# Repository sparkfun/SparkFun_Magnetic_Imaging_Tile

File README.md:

SparkFun Magnetic Imaging Tile - 8x8
========================================

[*SparkFun Magnetic Imaging Tile - 8x8 (SEN-26092)*](https://www.sparkfun.com/products/26092)

The Magnetic Imaging Tile uses an array of 64 hall effect sensors to convert magnetic fields to the visual spectrum. That's right! You can now see magnetic fields in real time! As is to be expected, there are caveats: the magnetic sensors used on the tile are some of the most sensitive on the market but you need to be within 1 to 2 centimeters of the tile to get a good image.

This is a board intended to function as a "magnetic field camera" to visualize magnetic fields.

This is an endorsed fork and collaboration of [Peter Jansen's work](https://hackaday.io/project/18518-iteration-8/log/91551-a-third-high-speed-magnetic-imager-tile). All credit goes to him! SparkX has re-designed the PCB for DFM and simplified some of the platform interfacing code.

### Version 3.0

The major advancement of v3.0 is a dramatic increase in the speed with which the tile data can be read out. ~2000 frames per second (fps) can be achieved which allows visualizing even quickly varying fields (e.g. those in a 60Hz transformer, or a moving motor). Version 3.0 reduces the size of the tile to an 8x8 grid of hall effect sensors (64 total), arrayed in a 4mm grid.  The boards is tile-able with up to 4 of the boards tileable with minimal borders to create a 16x16 array.

For more information (and a video of the v3.0 tile in use), please see:
https://hackaday.io/project/18518-iteration-8/log/91551-a-third-high-speed-magnetic-imager-tile-draft

Repository Contents
-------------------
* **.github/workflows** - YAML files used for GitHub Actions and GitHub Pages/mkdocs
* **/Hardware** - Eagle design files (.brd, .sch)
* **/Production** - Production panel files (.brd)
* **/Software** - Related software for the Magnetic Imaging Tile
* **/docs** - Online documentation files
  * **/assets** - Folder containing all the file assets used for product documentation
    * **/board_files** - Copy of design files used for product documentation
    * **/component_documentation** - Datasheets and manuals for hardware components
    * **/img** - Images for product documentation
  * **/github** - Files stating how to contribute and filing issues used for product documentation
  * **/javascript** - Folder containing custom javascript used for product documentation
  * **/stylesheet** - Folder containing CSS files used for product documentation
* **/overrides** - Customization files used for product documentation
  * **/.icons** - Icons used for GitHub used for product documentation
  * **./partials** - Used for product documentation

License Information
-------------------

This product is _**open source**_!

Please review the LICENSE.md file for license information.

If you have any questions or concerns on licensing, please contact technical support in our [SparkFun forums](https://community.sparkfun.com/c/community/general-chit-chat/37.)

Please use, reuse, and modify these files as you see fit. Please maintain attribution to SparkFun Electronics and release any derivative under the same license.

Disclaimer
-------------------

**DISCLAIMER OF WARRANTIES AND LIMITATION OF LIABILITY.**

UNLESS OTHERWISE SEPARATELY UNDERTAKEN BY THE LICENSOR, TO THE EXTENT POSSIBLE, THE LICENSOR OFFERS THE LICENSED MATERIAL AS-IS AND AS-AVAILABLE, AND MAKES NO REPRESENTATIONS OR WARRANTIES OF ANY KIND CONCERNING THE LICENSED MATERIAL, WHETHER EXPRESS, IMPLIED, STATUTORY, OR OTHER. THIS INCLUDES, WITHOUT LIMITATION, WARRANTIES OF TITLE, MERCHANTABILITY, FITNESS FOR A PARTICULAR PURPOSE, NON-INFRINGEMENT, ABSENCE OF LATENT OR OTHER DEFECTS, ACCURACY, OR THE PRESENCE OR ABSENCE OF ERRORS, WHETHER OR NOT KNOWN OR DISCOVERABLE. WHERE DISCLAIMERS OF WARRANTIES ARE NOT ALLOWED IN FULL OR IN PART, THIS DISCLAIMER MAY NOT APPLY TO YOU.

TO THE EXTENT POSSIBLE, IN NO EVENT WILL THE LICENSOR BE LIABLE TO YOU ON ANY LEGAL THEORY (INCLUDING, WITHOUT LIMITATION, NEGLIGENCE) OR OTHERWISE FOR ANY DIRECT, SPECIAL, INDIRECT, INCIDENTAL, CONSEQUENTIAL, PUNITIVE, EXEMPLARY, OR OTHER LOSSES, COSTS, EXPENSES, OR DAMAGES ARISING OUT OF THIS PUBLIC LICENSE OR USE OF THE LICENSED MATERIAL, EVEN IF THE LICENSOR HAS BEEN ADVISED OF THE POSSIBILITY OF SUCH LOSSES, COSTS, EXPENSES, OR DAMAGES. WHERE A LIMITATION OF LIABILITY IS NOT ALLOWED IN FULL OR IN PART, THIS LIMITATION MAY NOT APPLY TO YOU.

THE DISCLAIMER OF WARRANTIES AND LIMITATION OF LIABILITY PROVIDED ABOVE SHALL BE INTERPRETED IN A MANNER THAT, TO THE EXTENT POSSIBLE, MOST CLOSELY APPROXIMATES AN ABSOLUTE DISCLAIMER AND WAIVER OF ALL LIABILITY.

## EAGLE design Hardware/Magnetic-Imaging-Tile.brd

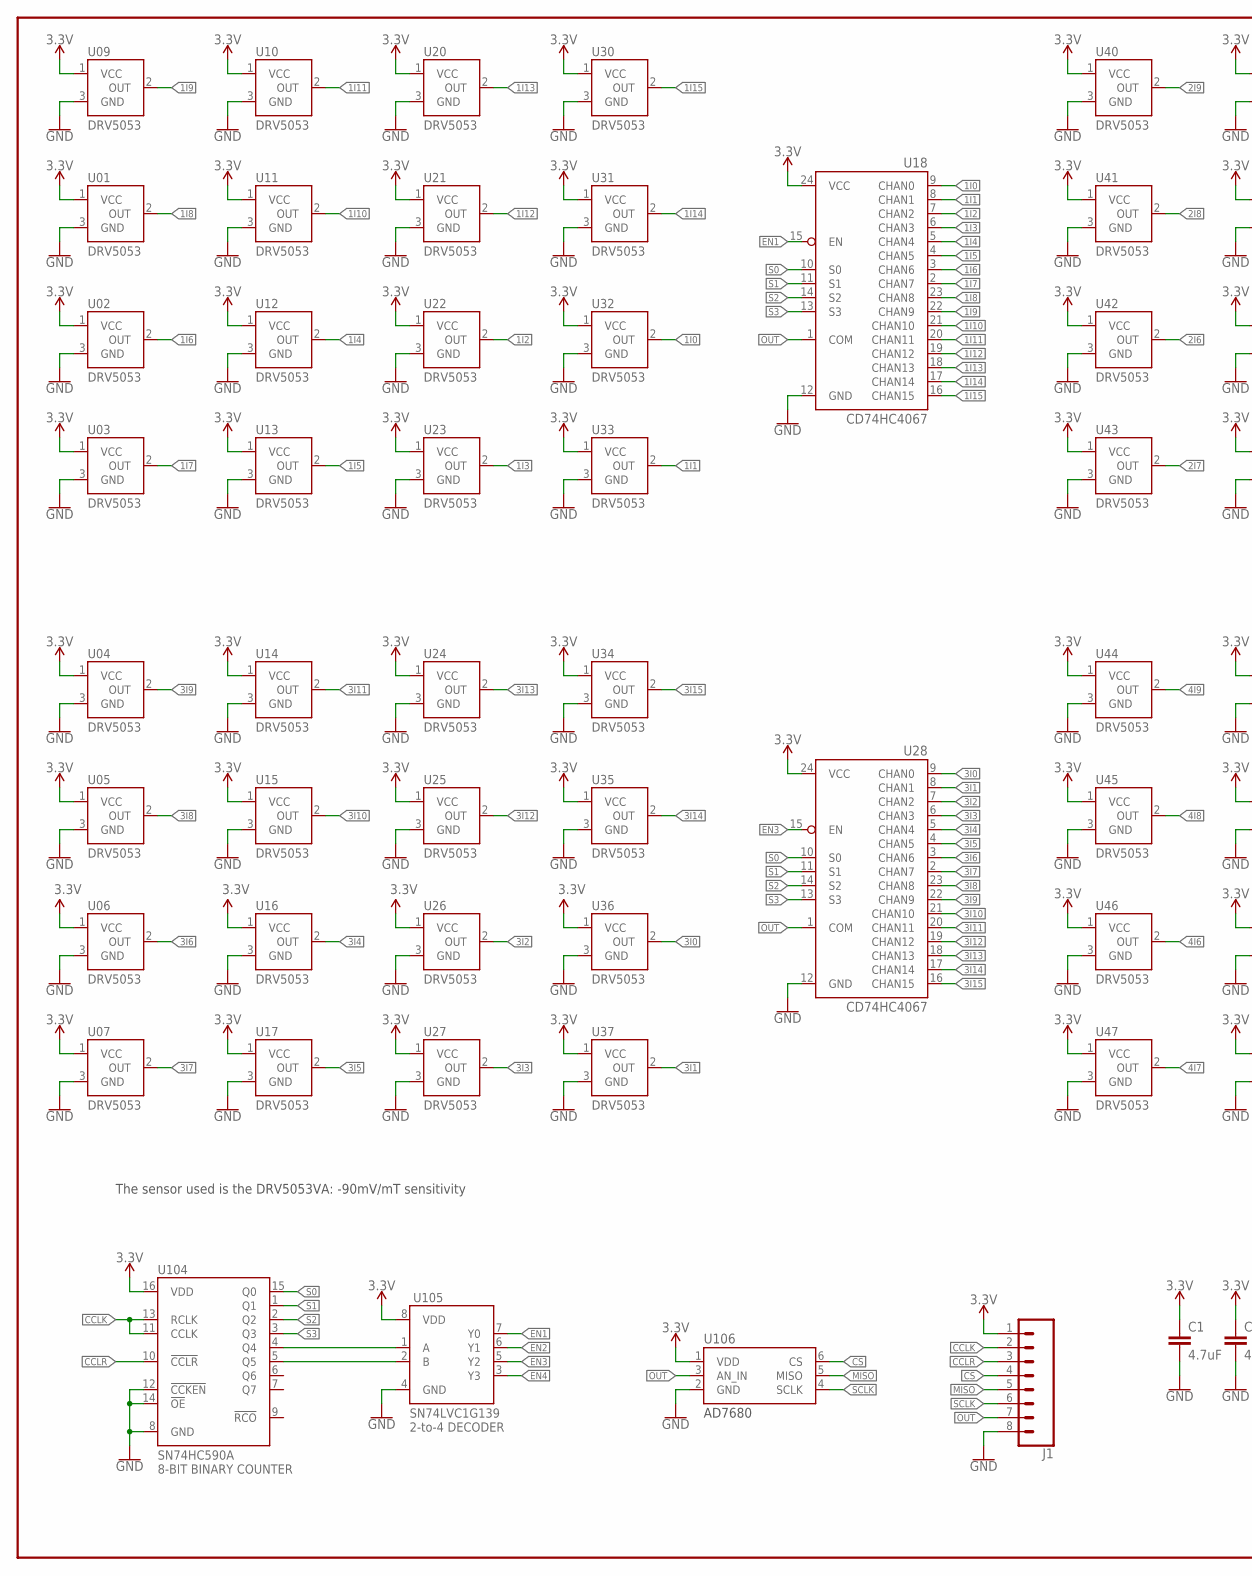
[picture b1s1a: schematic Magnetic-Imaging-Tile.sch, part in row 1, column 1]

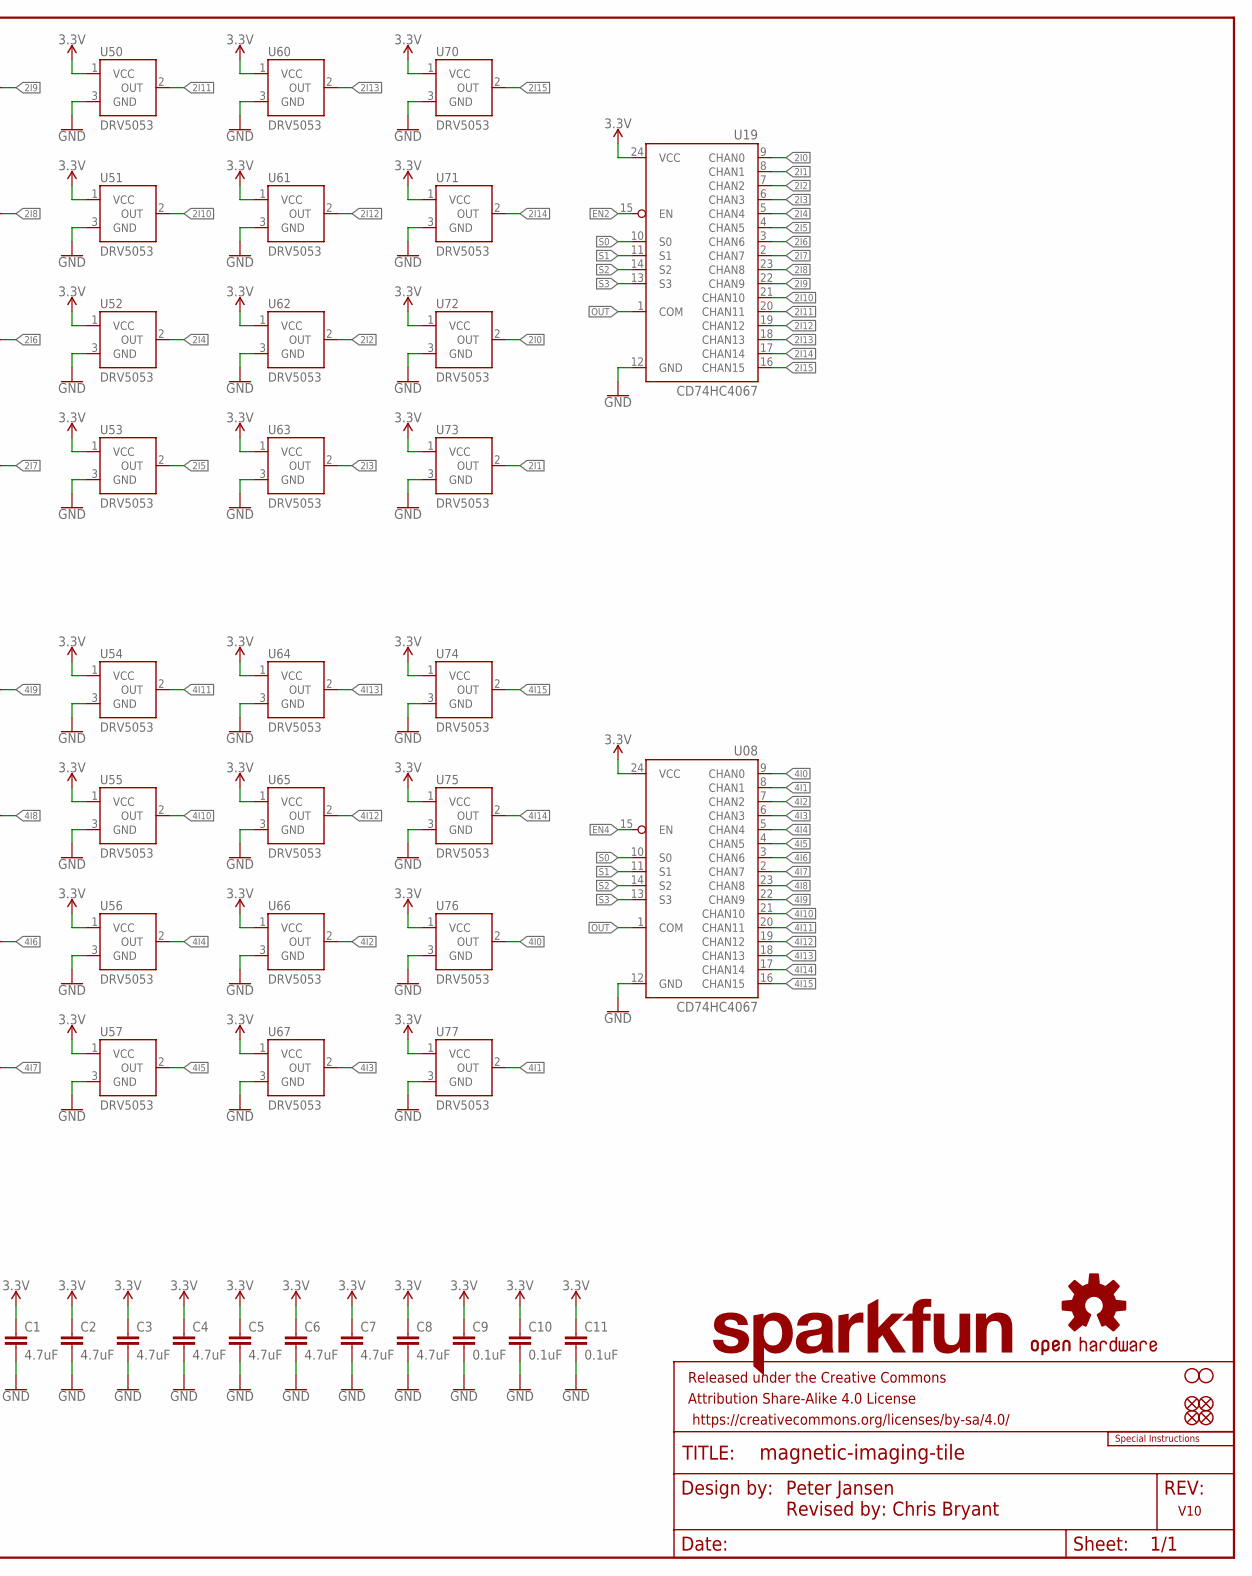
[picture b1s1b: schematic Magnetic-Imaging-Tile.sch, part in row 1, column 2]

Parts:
C1, C2, C3, C4, C5, C6, C7, C8: 4.7uF; 0603
C9, C10, C11: 0.1uF; 0603
FD1, FD2, FD3, FD4: FIDUCIALUFIDUCIAL; FIDUCIAL-MICRO
FRAME1: FRAME-LEDGER; CREATIVE_COMMONS
H1, H2: STAND-OFF
J1: CONN_08LOCK_NO_SILK; 1X08_LOCK_NO_SILK
LOGO1: SPECIAL_INSTRUCTIONS-ORDERING; ORDERING_INSTRUCTIONS
LOGO3: SFE_LOGO_NAME.1_INCH; SFE_LOGO_NAME_.1
LOGO4: OSHW-LOGOS; OSHW-LOGO-S
U01, U02, U03, U04, U05, U06, U07, U09, U10, U11, U12, U13, U14, U15, U16, U17, U20, U21, U22, U23, U24, U25, U26, U27, U30, U31, U32, U33, U34, U35, U36, U37, U40, U41, U42, U43, U44, U45, U46, U47, U50, U51, U52, U53, U54, U55, U56, U57, U60, U61, U62, U63, U64, U65, U66, U67, U70, U71, U72, U73, U74, U75, U76, U77: DRV5053; SOT23-3
U08, U18, U19, U28: CD74HC4067; SSOP24
U104: SN74HC590A; SO16
U105: SN74LVC1G139; SM8
U106: AD7680; SOT23-6

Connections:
1I0: U18.9 (CHAN0), U32.2 (OUT)
1I1: U18.8 (CHAN1), U33.2 (OUT)
1I2: U18.7 (CHAN2), U22.2 (OUT)
1I3: U18.6 (CHAN3), U23.2 (OUT)
1I4: U12.2 (OUT), U18.5 (CHAN4)
1I5: U13.2 (OUT), U18.4 (CHAN5)
1I6: U02.2 (OUT), U18.3 (CHAN6)
1I7: U03.2 (OUT), U18.2 (CHAN7)
1I8: U01.2 (OUT), U18.23 (CHAN8)
1I9: U09.2 (OUT), U18.22 (CHAN9)
1I10: U11.2 (OUT), U18.21 (CHAN10)
1I11: U10.2 (OUT), U18.20 (CHAN11)
1I12: U18.19 (CHAN12), U21.2 (OUT)
1I13: U18.18 (CHAN13), U20.2 (OUT)
1I14: U18.17 (CHAN14), U31.2 (OUT)
1I15: U18.16 (CHAN15), U30.2 (OUT)
2I0: U19.9 (CHAN0), U72.2 (OUT)
2I1: U19.8 (CHAN1), U73.2 (OUT)
2I2: U19.7 (CHAN2), U62.2 (OUT)
2I3: U19.6 (CHAN3), U63.2 (OUT)
2I4: U19.5 (CHAN4), U52.2 (OUT)
2I5: U19.4 (CHAN5), U53.2 (OUT)
2I6: U19.3 (CHAN6), U42.2 (OUT)
2I7: U19.2 (CHAN7), U43.2 (OUT)
2I8: U19.23 (CHAN8), U41.2 (OUT)
2I9: U19.22 (CHAN9), U40.2 (OUT)
2I10: U19.21 (CHAN10), U51.2 (OUT)
2I11: U19.20 (CHAN11), U50.2 (OUT)
2I12: U19.19 (CHAN12), U61.2 (OUT)
2I13: U19.18 (CHAN13), U60.2 (OUT)
2I14: U19.17 (CHAN14), U71.2 (OUT)
2I15: U19.16 (CHAN15), U70.2 (OUT)
3.3V: C1.1, C2.1, C3.1, C4.1, C5.1, C6.1, C7.1, C8.1, C9.1, C10.1, C11.1, J1.1, U01.1 (VCC), U02.1 (VCC), U03.1 (VCC), U04.1 (VCC), U05.1 (VCC), U06.1 (VCC), U07.1 (VCC), U08.24 (VCC), U09.1 (VCC), U10.1 (VCC), U11.1 (VCC), U12.1 (VCC), U13.1 (VCC), U14.1 (VCC), U15.1 (VCC), U16.1 (VCC), U17.1 (VCC), U18.24 (VCC), U19.24 (VCC), U20.1 (VCC), U21.1 (VCC), U22.1 (VCC), U23.1 (VCC), U24.1 (VCC), U25.1 (VCC), U26.1 (VCC), U27.1 (VCC), U28.24 (VCC), U30.1 (VCC), U31.1 (VCC), U32.1 (VCC), U33.1 (VCC), U34.1 (VCC), U35.1 (VCC), U36.1 (VCC), U37.1 (VCC), U40.1 (VCC), U41.1 (VCC), U42.1 (VCC), U43.1 (VCC), U44.1 (VCC), U45.1 (VCC), U46.1 (VCC), U47.1 (VCC), U50.1 (VCC), U51.1 (VCC), U52.1 (VCC), U53.1 (VCC), U54.1 (VCC), U55.1 (VCC), U56.1 (VCC), U57.1 (VCC), U60.1 (VCC), U61.1 (VCC), U62.1 (VCC), U63.1 (VCC), U64.1 (VCC), U65.1 (VCC), U66.1 (VCC), U67.1 (VCC), U70.1 (VCC), U71.1 (VCC), U72.1 (VCC), U73.1 (VCC), U74.1 (VCC), U75.1 (VCC), U76.1 (VCC), U77.1 (VCC), U104.16 (VDD), U105.8 (VDD), U106.1 (VDD)
3I0: U28.9 (CHAN0), U36.2 (OUT)
3I1: U28.8 (CHAN1), U37.2 (OUT)
3I2: U26.2 (OUT), U28.7 (CHAN2)
3I3: U27.2 (OUT), U28.6 (CHAN3)
3I4: U16.2 (OUT), U28.5 (CHAN4)
3I5: U17.2 (OUT), U28.4 (CHAN5)
3I6: U06.2 (OUT), U28.3 (CHAN6)
3I7: U07.2 (OUT), U28.2 (CHAN7)
3I8: U05.2 (OUT), U28.23 (CHAN8)
3I9: U04.2 (OUT), U28.22 (CHAN9)
3I10: U15.2 (OUT), U28.21 (CHAN10)
3I11: U14.2 (OUT), U28.20 (CHAN11)
3I12: U25.2 (OUT), U28.19 (CHAN12)
3I13: U24.2 (OUT), U28.18 (CHAN13)
3I14: U28.17 (CHAN14), U35.2 (OUT)
3I15: U28.16 (CHAN15), U34.2 (OUT)
4I0: U08.9 (CHAN0), U76.2 (OUT)
4I1: U08.8 (CHAN1), U77.2 (OUT)
4I2: U08.7 (CHAN2), U66.2 (OUT)
4I3: U08.6 (CHAN3), U67.2 (OUT)
4I4: U08.5 (CHAN4), U56.2 (OUT)
4I5: U08.4 (CHAN5), U57.2 (OUT)
4I6: U08.3 (CHAN6), U46.2 (OUT)
4I7: U08.2 (CHAN7), U47.2 (OUT)
4I8: U08.23 (CHAN8), U45.2 (OUT)
4I9: U08.22 (CHAN9), U44.2 (OUT)
4I10: U08.21 (CHAN10), U55.2 (OUT)
4I11: U08.20 (CHAN11), U54.2 (OUT)
4I12: U08.19 (CHAN12), U65.2 (OUT)
4I13: U08.18 (CHAN13), U64.2 (OUT)
4I14: U08.17 (CHAN14), U75.2 (OUT)
4I15: U08.16 (CHAN15), U74.2 (OUT)
!CCLR: J1.3, U104.10 (!CCLR)
!EN1: U18.15 (EN), U105.7 (Y0)
!EN2: U19.15 (EN), U105.6 (Y1)
!EN3: U28.15 (EN), U105.5 (Y2)
!EN4: U08.15 (EN), U105.3 (Y3)
CCLK: J1.2, U104.11 (CCLK), U104.13 (RCLK)
CS: J1.4, U106.6 (CS)
GND: C1.2, C2.2, C3.2, C4.2, C5.2, C6.2, C7.2, C8.2, C9.2, C10.2, C11.2, J1.8, U01.3 (GND), U02.3 (GND), U03.3 (GND), U04.3 (GND), U05.3 (GND), U06.3 (GND), U07.3 (GND), U08.12 (GND), U09.3 (GND), U10.3 (GND), U11.3 (GND), U12.3 (GND), U13.3 (GND), U14.3 (GND), U15.3 (GND), U16.3 (GND), U17.3 (GND), U18.12 (GND), U19.12 (GND), U20.3 (GND), U21.3 (GND), U22.3 (GND), U23.3 (GND), U24.3 (GND), U25.3 (GND), U26.3 (GND), U27.3 (GND), U28.12 (GND), U30.3 (GND), U31.3 (GND), U32.3 (GND), U33.3 (GND), U34.3 (GND), U35.3 (GND), U36.3 (GND), U37.3 (GND), U40.3 (GND), U41.3 (GND), U42.3 (GND), U43.3 (GND), U44.3 (GND), U45.3 (GND), U46.3 (GND), U47.3 (GND), U50.3 (GND), U51.3 (GND), U52.3 (GND), U53.3 (GND), U54.3 (GND), U55.3 (GND), U56.3 (GND), U57.3 (GND), U60.3 (GND), U61.3 (GND), U62.3 (GND), U63.3 (GND), U64.3 (GND), U65.3 (GND), U66.3 (GND), U67.3 (GND), U70.3 (GND), U71.3 (GND), U72.3 (GND), U73.3 (GND), U74.3 (GND), U75.3 (GND), U76.3 (GND), U77.3 (GND), U104.8 (GND), U104.12 (!CCKEN), U104.14 (!OE), U105.4 (GND), U106.2 (GND)
MISO: J1.5, U106.5 (MISO)
unnamed: U104.4 (Q4), U105.1 (A)
unnamed: U104.5 (Q5), U105.2 (B)
OUT: J1.7, U08.1 (COM), U18.1 (COM), U19.1 (COM), U28.1 (COM), U106.3 (AN_IN)
S0: U08.10 (S0), U18.10 (S0), U19.10 (S0), U28.10 (S0), U104.15 (Q0)
S1: U08.11 (S1), U18.11 (S1), U19.11 (S1), U28.11 (S1), U104.1 (Q1)
S2: U08.14 (S2), U18.14 (S2), U19.14 (S2), U28.14 (S2), U104.2 (Q2)
S3: U08.13 (S3), U18.13 (S3), U19.13 (S3), U28.13 (S3), U104.3 (Q3)
SCLK: J1.6, U106.4 (SCLK)

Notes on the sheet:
The sensor used is the DRV5053VA: -90mV/mT sensitivity
Peter Jansen Revised by: Chris Bryant
V10

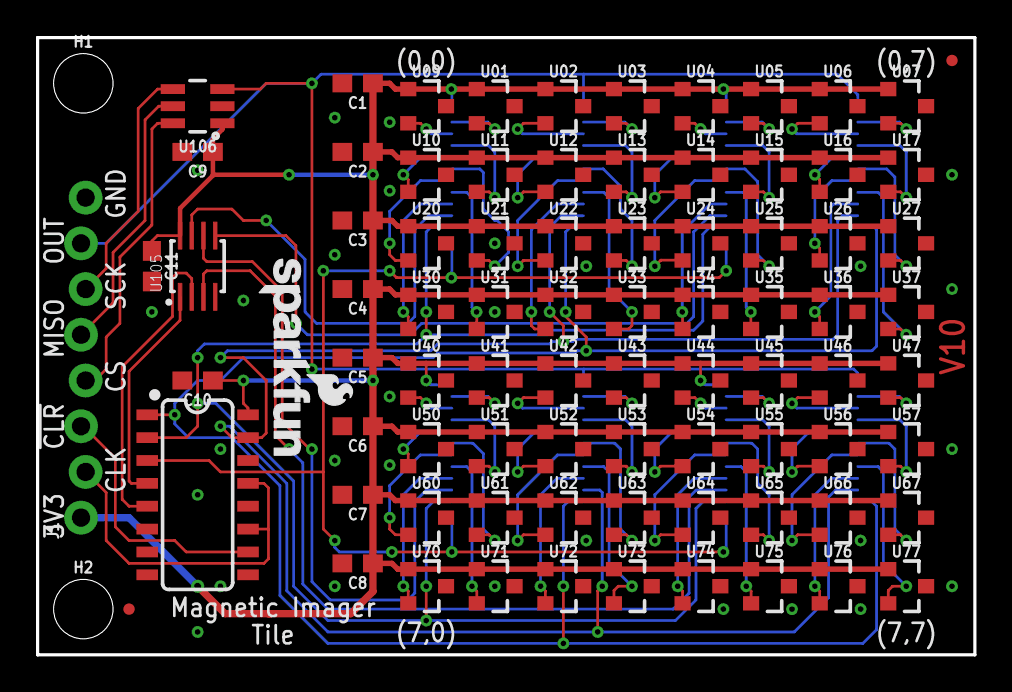
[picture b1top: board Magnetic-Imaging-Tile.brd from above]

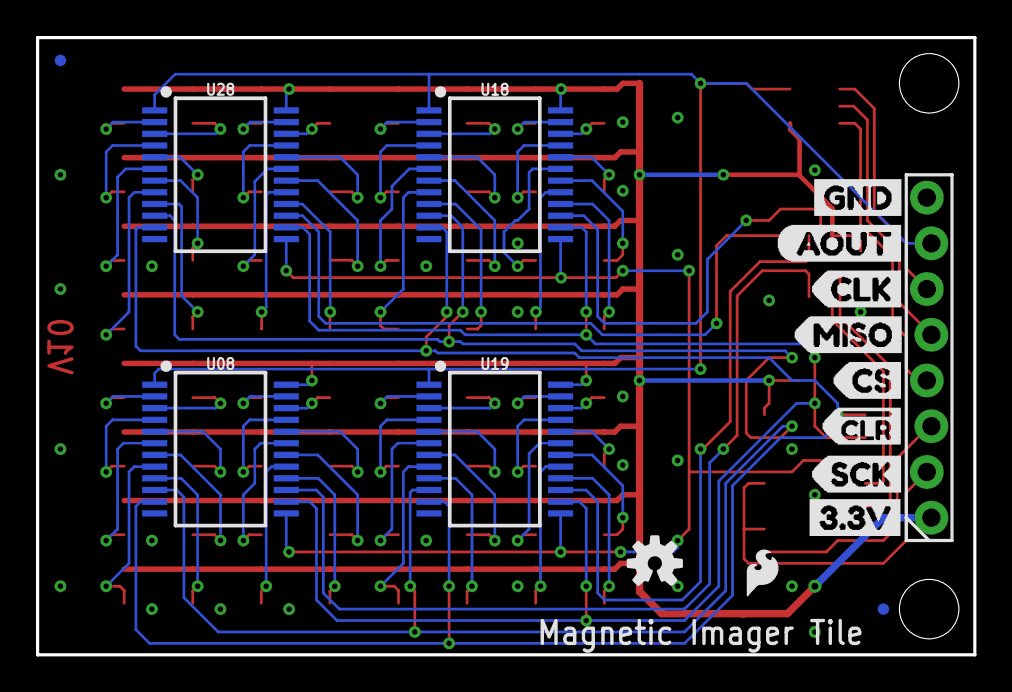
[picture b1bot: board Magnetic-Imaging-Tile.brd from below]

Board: 2 copper layers, 52.1 x 34.3 mm, 103 parts (16 on the bottom side), 82 nets.

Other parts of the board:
U$1, U$2: SFE_LOGO_FLAME_.1
U$3: GND
U$4: #CLR
U$5: 3#3V
U$6: AOUT
U$7: CLK
U$8: MISO
U$9: SCK
U$10: CS

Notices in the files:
parts and their libraries:
SparkFun-Connectors: Licensing: Creative Commons ShareAlike 4.0 International - https://creativecommons.org/licenses/by-sa/4.0
SparkFun-Aesthetics: Released under the Creative Commons Attribution Share-Alike 4.0 License
SparkFun-Aesthetics: https://creativecommons.org/licenses/by-sa/4.0
